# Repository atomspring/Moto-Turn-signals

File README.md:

# Moto-Turn-signals
Enhances old bike visibility by running turn signals at low current until needed. LED & Incandescent compatible.

See schematic: [Here](BTSE.pdf)

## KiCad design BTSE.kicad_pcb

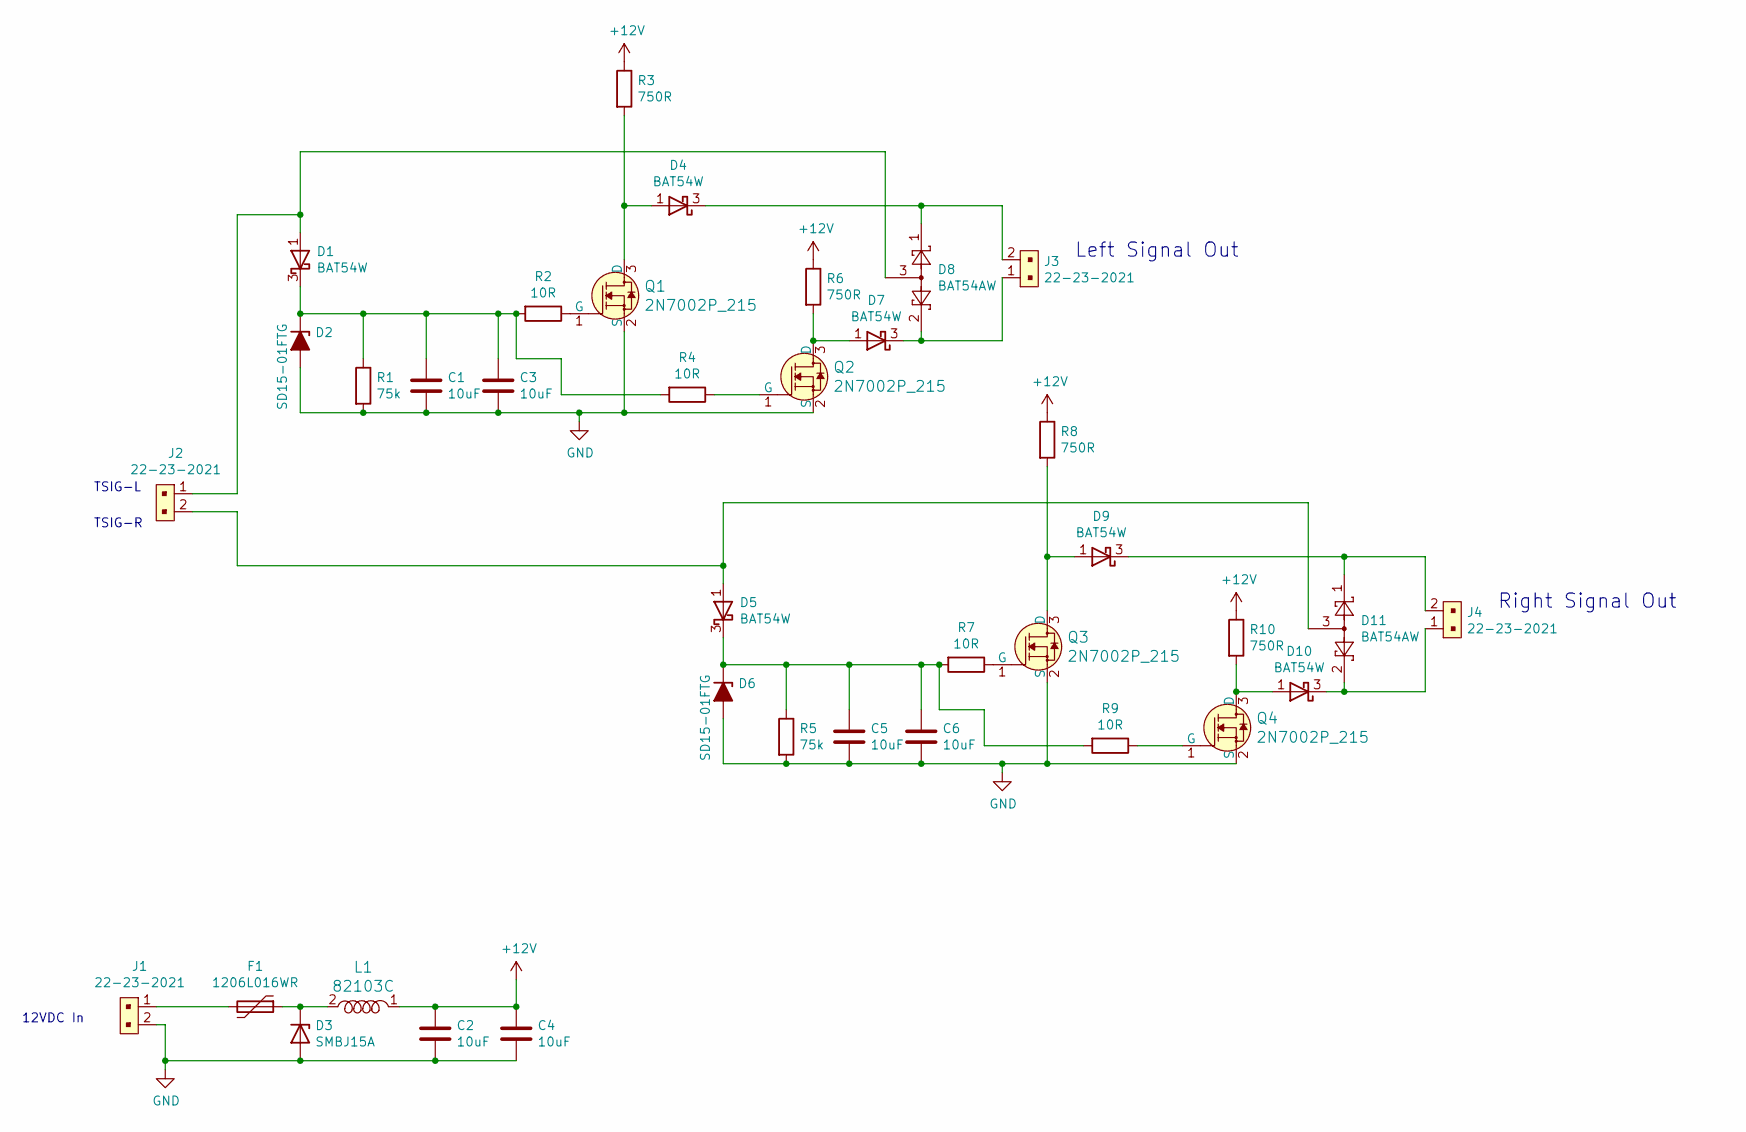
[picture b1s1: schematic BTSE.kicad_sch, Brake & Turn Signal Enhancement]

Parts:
C1, C3, C5, C6: 10uF; C_0805_2012Metric_Pad1.15x1.40mm_HandSolder
C2, C4: 10uF; C_1206_3216Metric_Pad1.42x1.75mm_HandSolder
D1, D4, D5, D7, D9, D10: BAT54W; SOT-323_SC-70
D2, D6: SD15-01FTG; D_SOD-323_HandSoldering
D3: SMBJ15A; D_SMB
D8, D11: BAT54AW; SOT-323_SC-70
F1: 1206L016WR; Fuse_1206_3216Metric
J1, J2, J3, J4: 22-23-2021; PinHeader_1x02_P2.54mm_Vertical; MPN 22-23-2021; Digi-Key_PN WM4200-ND
L1: 82103C; 1206; MPN 82103C; Digi-Key_PN 811-2473-1-ND
Q1, Q2, Q3, Q4: 2N7002P_215; SOT-23-3; MPN 2N7002P,215; Digi-Key_PN 1727-4692-1-ND
R1, R5: 75k; R_0805_2012Metric_Pad1.15x1.40mm_HandSolder
R2, R4, R7, R9: 10R; R_0805_2012Metric_Pad1.15x1.40mm_HandSolder
R3, R6, R8, R10: 750R; R_1210_3225Metric_Pad1.42x2.65mm_HandSolder

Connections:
+12V: C2.1, C4.1, L1.1, R3.1, R6.1, R8.1, R10.1
GND: C1.2, C2.2, C3.2, C4.2, C5.2, C6.2, D2.2 (A), D3.2 (A), D6.2 (A), J1.2, Q1.2 (S), Q2.2 (S), Q3.2 (S), Q4.2 (S), R1.2, R5.2
unnamed: D1.1 (A), D8.3, J2.1
unnamed: C1.1, C3.1, D1.3 (K), D2.1 (K), R1.1, R2.2, R4.2
unnamed: D3.1 (K), F1.1, L1.2
unnamed: D4.1 (A), Q1.3 (D), R3.2
unnamed: D4.3 (K), D8.1, J3.2
unnamed: D5.1 (A), D11.3, J2.2
unnamed: C5.1, C6.1, D5.3 (K), D6.1 (K), R5.1, R7.2, R9.2
unnamed: D7.1 (A), Q2.3 (D), R6.2
unnamed: D7.3 (K), D8.2, J3.1
unnamed: D9.1 (A), Q3.3 (D), R8.2
unnamed: D9.3 (K), D11.1, J4.2
unnamed: D10.1 (A), Q4.3 (D), R10.2
unnamed: D10.3 (K), D11.2, J4.1
unnamed: F1.2, J1.1
unnamed: Q1.1 (G), R2.1
unnamed: Q2.1 (G), R4.1
unnamed: Q3.1 (G), R7.1
unnamed: Q4.1 (G), R9.1

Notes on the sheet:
Left Signal Out
TSIG-R
TSIG-L
Right Signal Out
12VDC In

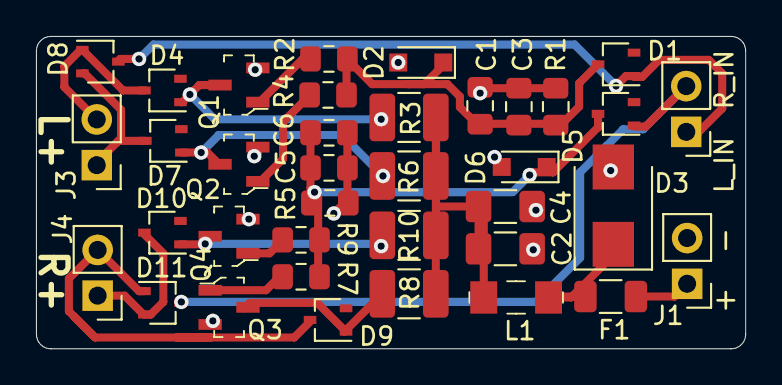
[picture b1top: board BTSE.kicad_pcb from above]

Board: 2 copper layers, 39.4 x 17.3 mm, 37 parts (0 on the bottom side), 20 nets.

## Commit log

2024-12-16 Create LICENSE
2024-12-16 Filled out readme a little
